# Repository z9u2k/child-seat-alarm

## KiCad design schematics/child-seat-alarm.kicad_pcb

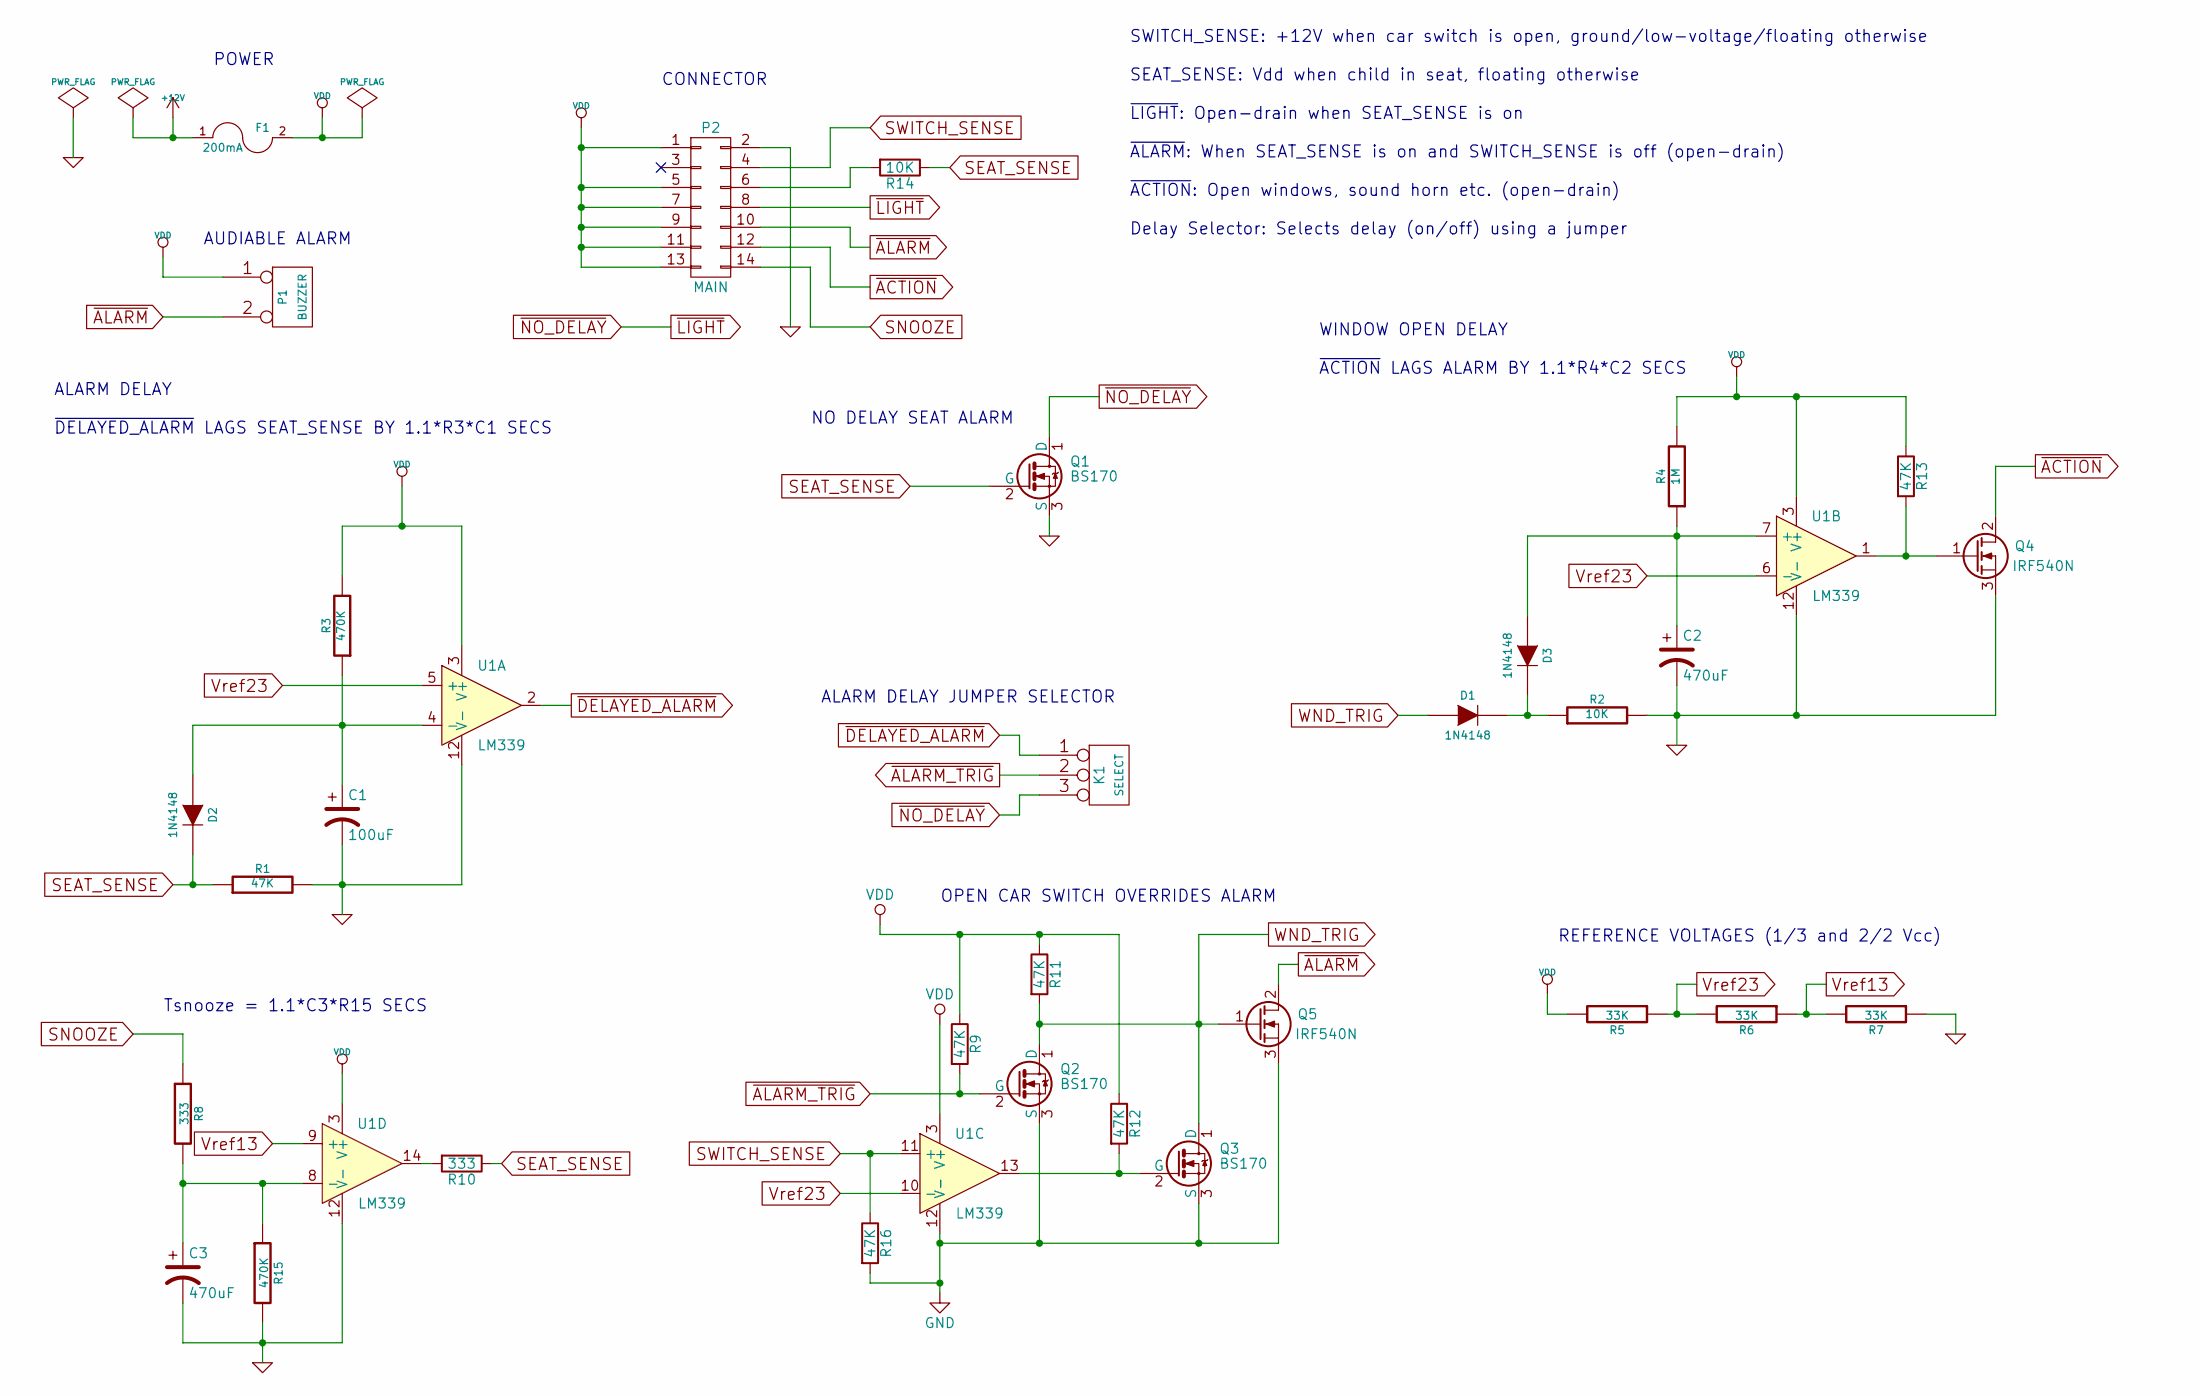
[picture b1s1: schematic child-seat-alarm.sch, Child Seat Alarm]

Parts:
C1: 100uF; C_Radial_D5_L11_P2.5
C2, C3: 470uF; C_Radial_D8_L11.5_P3.5
D1, D2, D3: 1N4148; Diode_DO-41_SOD81_Vertical_KathodeUp
F1: 200mA
K1: SELECT; Pin_Header_Straight_1x03
P1: BUZZER; Socket_MOLEX-KK-RM2-54mm_Lock_2pin_straight
P2: MAIN; Pin_Header_Straight_2x08
Q1, Q2, Q3: BS170; TO-92_Inline_Wide
Q4, Q5: IRF540N; TO-220
R1, R9, R11, R12, R13, R16: 47K; Resistor_Vertical_RM5mm
R2: 10K; Resistor_Vertical_RM5mm
R3, R15: 470K; Resistor_Vertical_RM5mm
R4: 1M; Resistor_Vertical_RM5mm
R5, R6, R7: 33K; R_0805_HandSoldering
R8: 333; Resistor_Vertical_RM5mm
R10: 333; Resistor_Horizontal_RM10mm
R14: 10K; R_0805_HandSoldering
U1: LM339; DIP-14_W7.62mm

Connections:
GND: C1.2, C2.2, C3.2, P2.2, Q1.3 (S), Q2.3 (S), Q3.3 (S), Q4.3 (S), Q5.3 (S), R1.2, R2.2, R7.1, R15.2, R16.2, U1.12 (V-)
unnamed: C1.1, D2.1 (A), R3.1, U1.4 (-)
unnamed: C2.1, D3.1 (A), R4.1, U1.7 (+)
unnamed: C3.1, R8.2, R15.1, U1.8 (-)
unnamed: D1.2 (K), D3.2 (K), R2.1
unnamed: P2.6, R14.2
unnamed: Q3.2 (G), R12.2, U1.13
unnamed: Q4.1 (G), R13.2, U1.1
unnamed: R10.2, U1.14
SEAT_SENSE: D2.2 (K), Q1.2 (G), R1.1, R10.1, R14.1
SNOOZE: P2.14, R8.1
SWITCH_SENSE: P2.4, R16.1, U1.11 (+)
VDD: F1.2, P1.1, P2.1, P2.5, P2.7, P2.9, P2.11, P2.13, R3.2, R4.2, R5.2, R9.1, R11.1, R12.1, R13.1, U1.3 (V+)
Vref13: R6.1, R7.2, U1.9 (+)
Vref23: R5.1, R6.2, U1.5 (+), U1.6 (-), U1.10 (-)
WND_TRIG: D1.1 (A), Q2.1 (D), Q3.1 (D), Q5.1 (G), R11.2
~ACTION: P2.12, Q4.2 (D)
~ALARM: P1.2 (PM), P2.10, Q5.2 (D)
~ALARM_TRIG: K1.2 (PM), Q2.2 (G), R9.2
~DELAYED_ALARM: K1.1, U1.2
~LIGHT: K1.3, P2.8, Q1.1 (D)

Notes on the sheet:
NO DELAY SEAT ALARM
OPEN CAR SWITCH OVERRIDES ALARM
ALARM DELAY JUMPER SELECTOR
WINDOW OPEN DELAY ~ACTION~ LAGS ALARM BY 1.1*R4*C2 SECS
AUDIABLE ALARM
POWER
SWITCH_SENSE: +12V when car switch is open, ground/low-voltage/floating otherwise SEAT_SENSE: Vdd when child in seat, floating otherwise ~LIGHT~: Open-drain when SEAT_SENSE is on ~ALARM~: When SEAT_SENSE is on and SWITCH_SENSE is off (open-drain) ~ACTION~: Open windows, sound horn etc. (open-drain)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
CONNECTOR
ALARM DELAY ~DELAYED_ALARM~ LAGS SEAT_SENSE BY 1.1*R3*C1 SECS
Tsnooze = 1.1*C3*R15 SECS
REFERENCE VOLTAGES (1/3 and 2/2 Vcc)

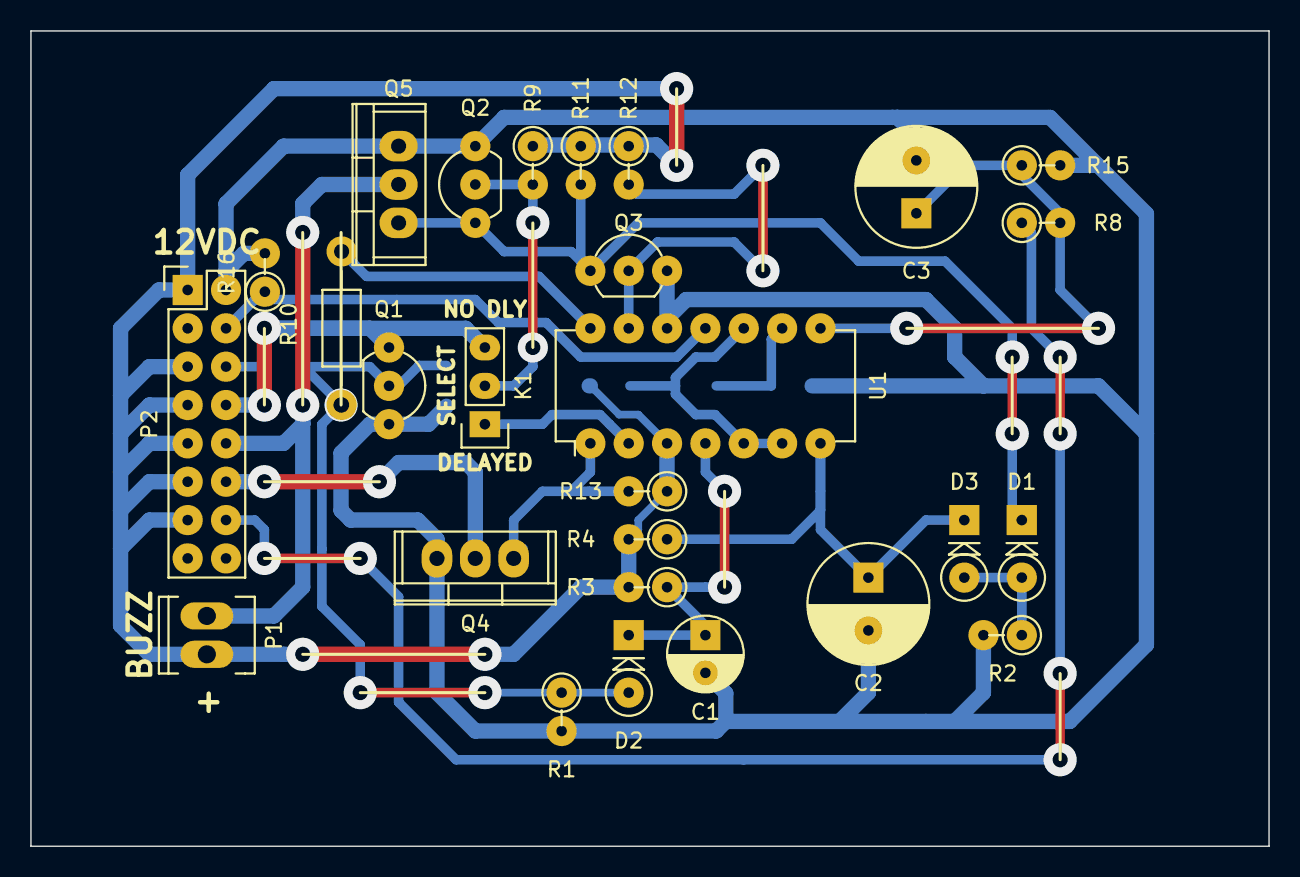
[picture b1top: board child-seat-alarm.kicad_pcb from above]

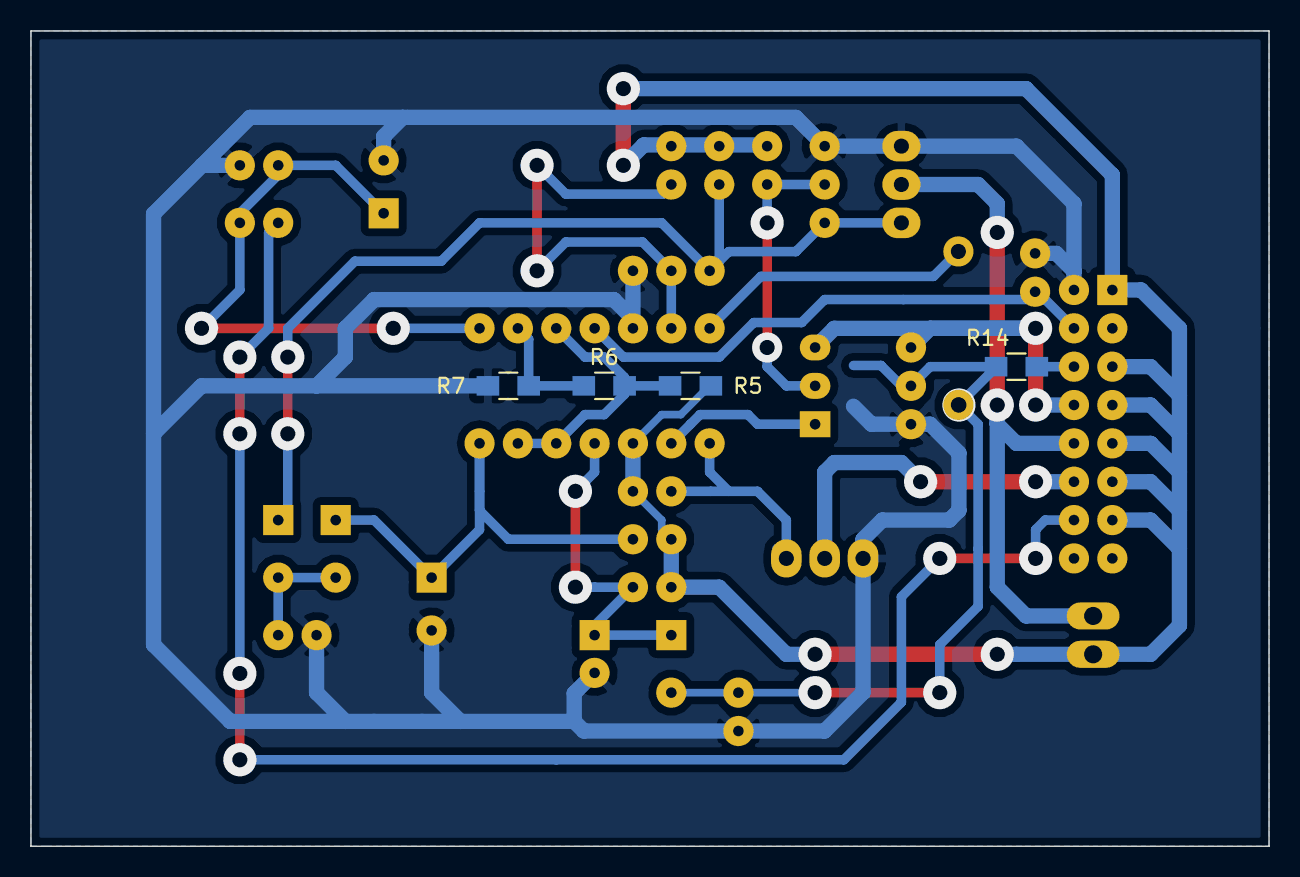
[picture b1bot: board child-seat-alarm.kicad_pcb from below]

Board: 2 copper layers, 82.0 x 54.0 mm, 31 parts (4 on the bottom side), 21 nets.
